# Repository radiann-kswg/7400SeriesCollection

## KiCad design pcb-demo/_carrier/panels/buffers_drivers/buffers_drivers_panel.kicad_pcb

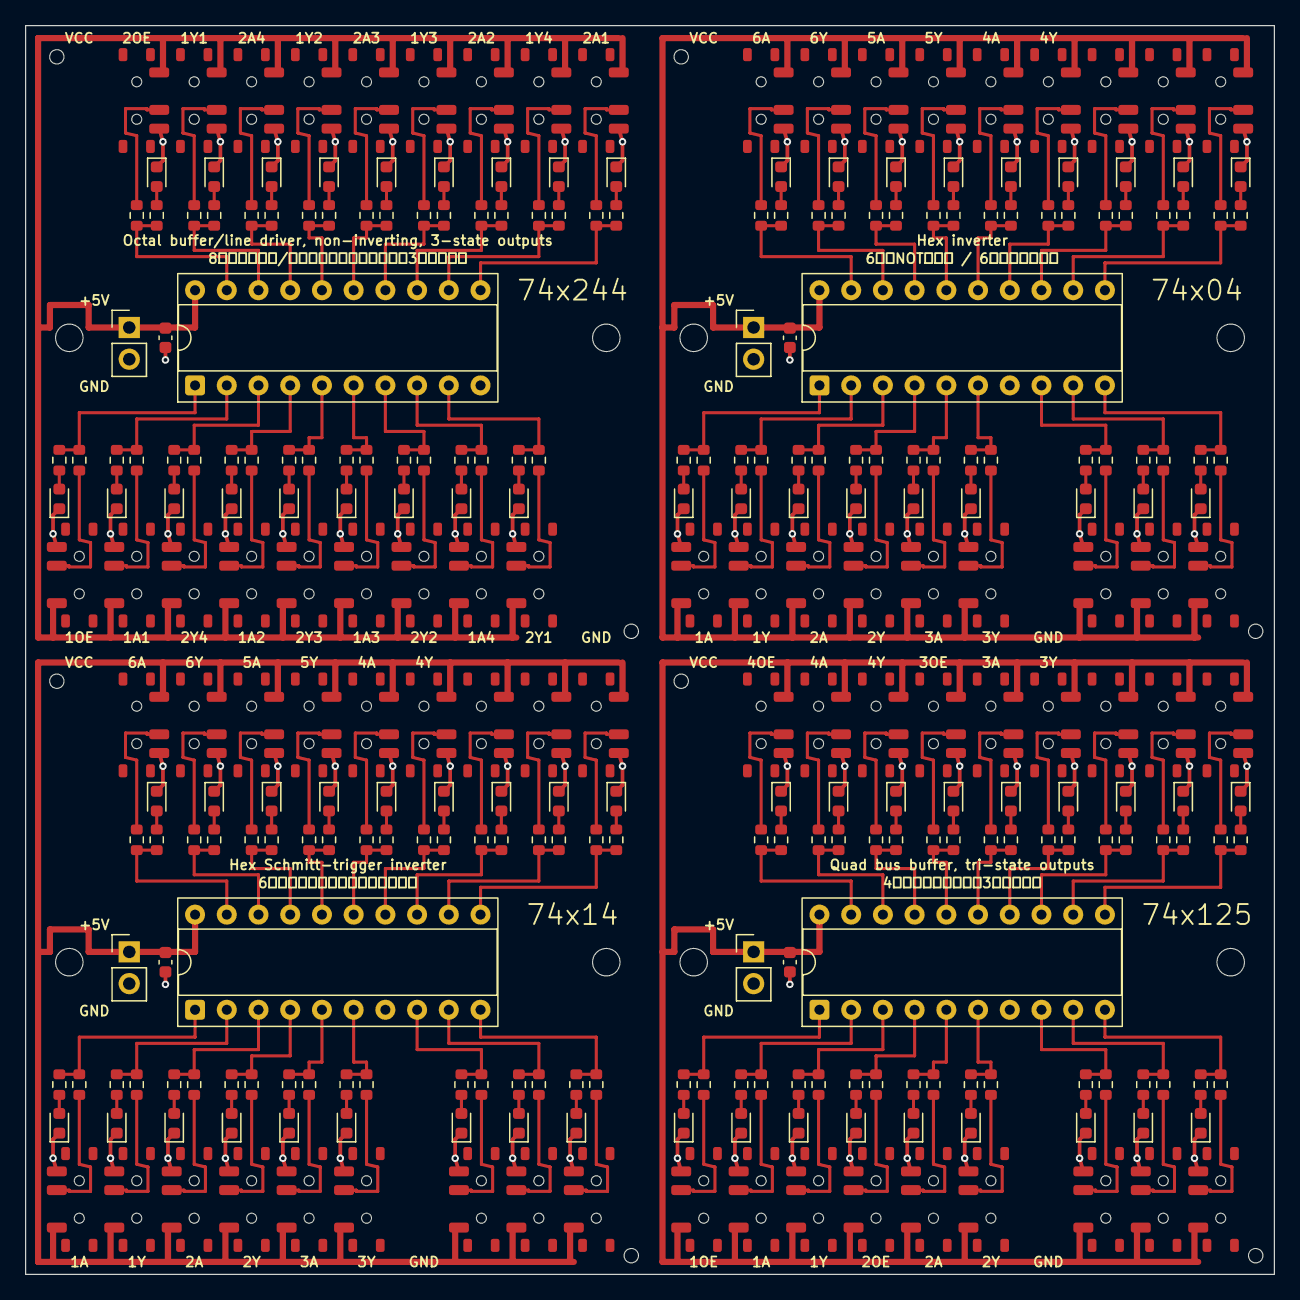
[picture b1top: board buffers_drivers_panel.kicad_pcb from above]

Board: 2 copper layers, 100.0 x 100.0 mm, 316 parts (0 on the bottom side), 224 nets.

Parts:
A_C1: 100nF; C_0603_1608Metric
A_D1, A_D2, A_D4, A_D6, A_D8, A_D11, A_D13, A_D15, A_D17, A_D19: RED; LED_0603_1608Metric
A_D3, A_D5, A_D7, A_D9, A_D12, A_D14, A_D16, A_D18: WHITE; LED_0603_1608Metric
A_J1: 5V_IN; PinHeader_1x02_P2.54mm_Vertical
A_MTG1, A_MTG2: MountingHole_2.2mm_M2
A_R1, A_R2, A_R3, A_R4, A_R5, A_R6, A_R7, A_R8, A_R9, A_R11, A_R12, A_R13, A_R14, A_R15, A_R16, A_R17, A_R18, A_R19: 4.7k; R_0603_1608Metric
A_R21, A_R22, A_R23, A_R24, A_R25, A_R26, A_R27, A_R28, A_R29, A_R31, A_R32, A_R33, A_R34, A_R35, A_R36, A_R37, A_R38, A_R39: 220; R_0603_1608Metric
A_SW1, A_SW2, A_SW3, A_SW4, A_SW5, A_SW6, A_SW7, A_SW8, A_SW9, A_SW11, A_SW12, A_SW13, A_SW14, A_SW15, A_SW16, A_SW17, A_SW18, A_SW19: MSS12C02LS-BB2.0; SW_SPDT_Shouhan_MSS12C02LS
A_TH1, A_TH2: ToolingHole_1.152mm
A_U1: DIP20_Socket_300mil; DIP-20_W7.62mm_Socket
B_C1: 100nF; C_0603_1608Metric
B_D1, B_D3, B_D5, B_D8, B_D9, B_D10, B_D11, B_D12, B_D13, B_D15, B_D17, B_D19: RED; LED_0603_1608Metric
B_D2, B_D4, B_D6, B_D14, B_D16, B_D18: WHITE; LED_0603_1608Metric
B_J1: 5V_IN; PinHeader_1x02_P2.54mm_Vertical
B_MTG1, B_MTG2: MountingHole_2.2mm_M2
B_R1, B_R2, B_R3, B_R4, B_R5, B_R6, B_R8, B_R9, B_R10, B_R11, B_R12, B_R13, B_R14, B_R15, B_R16, B_R17, B_R18, B_R19: 4.7k; R_0603_1608Metric
B_R21, B_R22, B_R23, B_R24, B_R25, B_R26, B_R28, B_R29, B_R30, B_R31, B_R32, B_R33, B_R34, B_R35, B_R36, B_R37, B_R38, B_R39: 220; R_0603_1608Metric
B_SW1, B_SW2, B_SW3, B_SW4, B_SW5, B_SW6, B_SW8, B_SW9, B_SW10, B_SW11, B_SW12, B_SW13, B_SW14, B_SW15, B_SW16, B_SW17, B_SW18, B_SW19: MSS12C02LS-BB2.0; SW_SPDT_Shouhan_MSS12C02LS
B_TH1, B_TH2: ToolingHole_1.152mm
B_U1: DIP20_Socket_300mil; DIP-20_W7.62mm_Socket
C_C1: 100nF; C_0603_1608Metric
C_D1, C_D3, C_D5, C_D8, C_D9, C_D10, C_D11, C_D12, C_D13, C_D15, C_D17, C_D19: RED; LED_0603_1608Metric
C_D2, C_D4, C_D6, C_D14, C_D16, C_D18: WHITE; LED_0603_1608Metric
C_J1: 5V_IN; PinHeader_1x02_P2.54mm_Vertical
C_MTG1, C_MTG2: MountingHole_2.2mm_M2
C_R1, C_R2, C_R3, C_R4, C_R5, C_R6, C_R8, C_R9, C_R10, C_R11, C_R12, C_R13, C_R14, C_R15, C_R16, C_R17, C_R18, C_R19: 4.7k; R_0603_1608Metric
C_R21, C_R22, C_R23, C_R24, C_R25, C_R26, C_R28, C_R29, C_R30, C_R31, C_R32, C_R33, C_R34, C_R35, C_R36, C_R37, C_R38, C_R39: 220; R_0603_1608Metric
C_SW1, C_SW2, C_SW3, C_SW4, C_SW5, C_SW6, C_SW8, C_SW9, C_SW10, C_SW11, C_SW12, C_SW13, C_SW14, C_SW15, C_SW16, C_SW17, C_SW18, C_SW19: MSS12C02LS-BB2.0; SW_SPDT_Shouhan_MSS12C02LS
C_TH1, C_TH2: ToolingHole_1.152mm
C_U1: DIP20_Socket_300mil; DIP-20_W7.62mm_Socket
D_C1: 100nF; C_0603_1608Metric
D_D1, D_D2, D_D4, D_D5, D_D8, D_D9, D_D10, D_D11, D_D12, D_D13, D_D15, D_D16, D_D18, D_D19: RED; LED_0603_1608Metric
D_D3, D_D6, D_D14, D_D17: WHITE; LED_0603_1608Metric
D_J1: 5V_IN; PinHeader_1x02_P2.54mm_Vertical
D_MTG1, D_MTG2: MountingHole_2.2mm_M2
D_R1, D_R2, D_R3, D_R4, D_R5, D_R6, D_R8, D_R9, D_R10, D_R11, D_R12, D_R13, D_R14, D_R15, D_R16, D_R17, D_R18, D_R19: 4.7k; R_0603_1608Metric
D_R21, D_R22, D_R23, D_R24, D_R25, D_R26, D_R28, D_R29, D_R30, D_R31, D_R32, D_R33, D_R34, D_R35, D_R36, D_R37, D_R38, D_R39: 220; R_0603_1608Metric
D_SW1, D_SW2, D_SW3, D_SW4, D_SW5, D_SW6, D_SW8, D_SW9, D_SW10, D_SW11, D_SW12, D_SW13, D_SW14, D_SW15, D_SW16, D_SW17, D_SW18, D_SW19: MSS12C02LS-BB2.0; SW_SPDT_Shouhan_MSS12C02LS
D_TH1, D_TH2: ToolingHole_1.152mm
D_U1: DIP20_Socket_300mil; DIP-20_W7.62mm_Socket

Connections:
A_+5V: A_C1.1, A_J1.1, A_SW1.1, A_SW2.1, A_SW3.1, A_SW4.1, A_SW5.1, A_SW6.1, A_SW7.1, A_SW8.1, A_SW9.1, A_SW11.1, A_SW12.1, A_SW13.1, A_SW14.1, A_SW15.1, A_SW16.1, A_SW17.1, A_SW18.1, A_SW19.1, A_U1.20
A_/LA1: A_D1.2, A_R1.1
A_/LA2: A_D2.2, A_R2.1
A_/LA3: A_D3.2, A_R3.1
A_/LA4: A_D4.2, A_R4.1
A_/LA5: A_D5.2, A_R5.1
A_/LA6: A_D6.2, A_R6.1
A_/LA7: A_D7.2, A_R7.1
A_/LA8: A_D8.2, A_R8.1
A_/LA9: A_D9.2, A_R9.1
A_/LA11: A_D11.2, A_R11.1
A_/LA12: A_D12.2, A_R12.1
A_/LA13: A_D13.2, A_R13.1
A_/LA14: A_D14.2, A_R14.1
A_/LA15: A_D15.2, A_R15.1
A_/LA16: A_D16.2, A_R16.1
A_/LA17: A_D17.2, A_R17.1
A_/LA18: A_D18.2, A_R18.1
A_/LA19: A_D19.2, A_R19.1
A_/P1: A_R1.2, A_R21.2, A_U1.1
A_/P2: A_R2.2, A_R22.2, A_U1.2
A_/P3: A_R3.2, A_R23.2, A_U1.3
A_/P4: A_R4.2, A_R24.2, A_U1.4
A_/P5: A_R5.2, A_R25.2, A_U1.5
A_/P6: A_R6.2, A_R26.2, A_U1.6
A_/P7: A_R7.2, A_R27.2, A_U1.7
A_/P8: A_R8.2, A_R28.2, A_U1.8
A_/P9: A_R9.2, A_R29.2, A_U1.9
A_/P11: A_R11.2, A_R31.2, A_U1.11
A_/P12: A_R12.2, A_R32.2, A_U1.12
A_/P13: A_R13.2, A_R33.2, A_U1.13
A_/P14: A_R14.2, A_R34.2, A_U1.14
A_/P15: A_R15.2, A_R35.2, A_U1.15
A_/P16: A_R16.2, A_R36.2, A_U1.16
A_/P17: A_R17.2, A_R37.2, A_U1.17
A_/P18: A_R18.2, A_R38.2, A_U1.18
A_/P19: A_R19.2, A_R39.2, A_U1.19
A_/SWC1: A_R21.1, A_SW1.2
A_/SWC2: A_R22.1, A_SW2.2
A_/SWC3: A_R23.1, A_SW3.2
A_/SWC4: A_R24.1, A_SW4.2
A_/SWC5: A_R25.1, A_SW5.2
A_/SWC6: A_R26.1, A_SW6.2
A_/SWC7: A_R27.1, A_SW7.2
A_/SWC8: A_R28.1, A_SW8.2
A_/SWC9: A_R29.1, A_SW9.2
A_/SWC11: A_R31.1, A_SW11.2
A_/SWC12: A_R32.1, A_SW12.2
A_/SWC13: A_R33.1, A_SW13.2
A_/SWC14: A_R34.1, A_SW14.2
A_/SWC15: A_R35.1, A_SW15.2
A_/SWC16: A_R36.1, A_SW16.2
A_/SWC17: A_R37.1, A_SW17.2
A_/SWC18: A_R38.1, A_SW18.2
A_/SWC19: A_R39.1, A_SW19.2
A_GND: A_C1.2, A_D1.1, A_D2.1, A_D3.1, A_D4.1, A_D5.1, A_D6.1, A_D7.1, A_D8.1, A_D9.1, A_D11.1, A_D12.1, A_D13.1, A_D14.1, A_D15.1, A_D16.1, A_D17.1, A_D18.1, A_D19.1, A_J1.2, A_SW1.3, A_SW2.3, A_SW3.3, A_SW4.3, A_SW5.3, A_SW6.3, A_SW7.3, A_SW8.3, A_SW9.3, A_SW11.3, A_SW12.3, A_SW13.3, A_SW14.3, A_SW15.3, A_SW16.3, A_SW17.3, A_SW18.3, A_SW19.3, A_U1.10
B_+5V: B_C1.1, B_J1.1, B_SW1.1, B_SW2.1, B_SW3.1, B_SW4.1, B_SW5.1, B_SW6.1, B_SW8.1, B_SW9.1, B_SW10.1, B_SW11.1, B_SW12.1, B_SW13.1, B_SW14.1, B_SW15.1, B_SW16.1, B_SW17.1, B_SW18.1, B_SW19.1, B_U1.20
B_/LA1: B_D1.2, B_R1.1
B_/LA2: B_D2.2, B_R2.1
B_/LA3: B_D3.2, B_R3.1
B_/LA4: B_D4.2, B_R4.1
B_/LA5: B_D5.2, B_R5.1
B_/LA6: B_D6.2, B_R6.1
B_/LA8: B_D8.2, B_R8.1
B_/LA9: B_D9.2, B_R9.1
B_/LA10: B_D10.2, B_R10.1
B_/LA11: B_D11.2, B_R11.1
B_/LA12: B_D12.2, B_R12.1
B_/LA13: B_D13.2, B_R13.1
B_/LA14: B_D14.2, B_R14.1
B_/LA15: B_D15.2, B_R15.1
B_/LA16: B_D16.2, B_R16.1
B_/LA17: B_D17.2, B_R17.1
B_/LA18: B_D18.2, B_R18.1
B_/LA19: B_D19.2, B_R19.1
B_/P1: B_R1.2, B_R21.2, B_U1.1
B_/P2: B_R2.2, B_R22.2, B_U1.2
B_/P3: B_R3.2, B_R23.2, B_U1.3
B_/P4: B_R4.2, B_R24.2, B_U1.4
B_/P5: B_R5.2, B_R25.2, B_U1.5
B_/P6: B_R6.2, B_R26.2, B_U1.6
B_/P8: B_R8.2, B_R28.2, B_U1.8
B_/P9: B_R9.2, B_R29.2, B_U1.9
B_/P10: B_R10.2, B_R30.2, B_U1.10
B_/P11: B_R11.2, B_R31.2, B_U1.11
B_/P12: B_R12.2, B_R32.2, B_U1.12
B_/P13: B_R13.2, B_R33.2, B_U1.13
B_/P14: B_R14.2, B_R34.2, B_U1.14
B_/P15: B_R15.2, B_R35.2, B_U1.15
B_/P16: B_R16.2, B_R36.2, B_U1.16
B_/P17: B_R17.2, B_R37.2, B_U1.17
B_/P18: B_R18.2, B_R38.2, B_U1.18
B_/P19: B_R19.2, B_R39.2, B_U1.19
B_/SWC1: B_R21.1, B_SW1.2
B_/SWC2: B_R22.1, B_SW2.2
B_/SWC3: B_R23.1, B_SW3.2
B_/SWC4: B_R24.1, B_SW4.2
B_/SWC5: B_R25.1, B_SW5.2
B_/SWC6: B_R26.1, B_SW6.2
B_/SWC8: B_R28.1, B_SW8.2
B_/SWC9: B_R29.1, B_SW9.2
B_/SWC10: B_R30.1, B_SW10.2
B_/SWC11: B_R31.1, B_SW11.2
B_/SWC12: B_R32.1, B_SW12.2
B_/SWC13: B_R33.1, B_SW13.2
B_/SWC14: B_R34.1, B_SW14.2
B_/SWC15: B_R35.1, B_SW15.2
B_/SWC16: B_R36.1, B_SW16.2
B_/SWC17: B_R37.1, B_SW17.2
B_/SWC18: B_R38.1, B_SW18.2
B_/SWC19: B_R39.1, B_SW19.2
B_GND: B_C1.2, B_D1.1, B_D2.1, B_D3.1, B_D4.1, B_D5.1, B_D6.1, B_D8.1, B_D9.1, B_D10.1, B_D11.1, B_D12.1, B_D13.1, B_D14.1, B_D15.1, B_D16.1, B_D17.1, B_D18.1, B_D19.1, B_J1.2, B_SW1.3, B_SW2.3, B_SW3.3, B_SW4.3, B_SW5.3, B_SW6.3, B_SW8.3, B_SW9.3, B_SW10.3, B_SW11.3, B_SW12.3, B_SW13.3, B_SW14.3, B_SW15.3, B_SW16.3, B_SW17.3, B_SW18.3, B_SW19.3, B_U1.7
C_+5V: C_C1.1, C_J1.1, C_SW1.1, C_SW2.1, C_SW3.1, C_SW4.1, C_SW5.1, C_SW6.1, C_SW8.1, C_SW9.1, C_SW10.1, C_SW11.1, C_SW12.1, C_SW13.1, C_SW14.1, C_SW15.1, C_SW16.1, C_SW17.1, C_SW18.1, C_SW19.1, C_U1.20
C_/LA1: C_D1.2, C_R1.1
C_/LA2: C_D2.2, C_R2.1
C_/LA3: C_D3.2, C_R3.1
C_/LA4: C_D4.2, C_R4.1
C_/LA5: C_D5.2, C_R5.1
C_/LA6: C_D6.2, C_R6.1
C_/LA8: C_D8.2, C_R8.1
C_/LA9: C_D9.2, C_R9.1
C_/LA10: C_D10.2, C_R10.1
C_/LA11: C_D11.2, C_R11.1
C_/LA12: C_D12.2, C_R12.1
C_/LA13: C_D13.2, C_R13.1
C_/LA14: C_D14.2, C_R14.1
C_/LA15: C_D15.2, C_R15.1
C_/LA16: C_D16.2, C_R16.1
C_/LA17: C_D17.2, C_R17.1
C_/LA18: C_D18.2, C_R18.1
C_/LA19: C_D19.2, C_R19.1
C_/P1: C_R1.2, C_R21.2, C_U1.1
C_/P2: C_R2.2, C_R22.2, C_U1.2
C_/P3: C_R3.2, C_R23.2, C_U1.3
C_/P4: C_R4.2, C_R24.2, C_U1.4
C_/P5: C_R5.2, C_R25.2, C_U1.5
C_/P6: C_R6.2, C_R26.2, C_U1.6
C_/P8: C_R8.2, C_R28.2, C_U1.8
C_/P9: C_R9.2, C_R29.2, C_U1.9
C_/P10: C_R10.2, C_R30.2, C_U1.10
C_/P11: C_R11.2, C_R31.2, C_U1.11
C_/P12: C_R12.2, C_R32.2, C_U1.12
C_/P13: C_R13.2, C_R33.2, C_U1.13
C_/P14: C_R14.2, C_R34.2, C_U1.14
C_/P15: C_R15.2, C_R35.2, C_U1.15
C_/P16: C_R16.2, C_R36.2, C_U1.16
C_/P17: C_R17.2, C_R37.2, C_U1.17
C_/P18: C_R18.2, C_R38.2, C_U1.18
C_/P19: C_R19.2, C_R39.2, C_U1.19
C_/SWC1: C_R21.1, C_SW1.2
C_/SWC2: C_R22.1, C_SW2.2
C_/SWC3: C_R23.1, C_SW3.2
C_/SWC4: C_R24.1, C_SW4.2
C_/SWC5: C_R25.1, C_SW5.2
C_/SWC6: C_R26.1, C_SW6.2
C_/SWC8: C_R28.1, C_SW8.2
C_/SWC9: C_R29.1, C_SW9.2
C_/SWC10: C_R30.1, C_SW10.2
C_/SWC11: C_R31.1, C_SW11.2
C_/SWC12: C_R32.1, C_SW12.2
C_/SWC13: C_R33.1, C_SW13.2
C_/SWC14: C_R34.1, C_SW14.2
C_/SWC15: C_R35.1, C_SW15.2
C_/SWC16: C_R36.1, C_SW16.2
C_/SWC17: C_R37.1, C_SW17.2
C_/SWC18: C_R38.1, C_SW18.2
C_/SWC19: C_R39.1, C_SW19.2
C_GND: C_C1.2, C_D1.1, C_D2.1, C_D3.1, C_D4.1, C_D5.1, C_D6.1, C_D8.1, C_D9.1, C_D10.1, C_D11.1, C_D12.1, C_D13.1, C_D14.1, C_D15.1, C_D16.1, C_D17.1, C_D18.1, C_D19.1, C_J1.2, C_SW1.3, C_SW2.3, C_SW3.3, C_SW4.3, C_SW5.3, C_SW6.3, C_SW8.3, C_SW9.3, C_SW10.3, C_SW11.3, C_SW12.3, C_SW13.3, C_SW14.3, C_SW15.3, C_SW16.3, C_SW17.3, C_SW18.3, C_SW19.3, C_U1.7
D_+5V: D_C1.1, D_J1.1, D_SW1.1, D_SW2.1, D_SW3.1, D_SW4.1, D_SW5.1, D_SW6.1, D_SW8.1, D_SW9.1, D_SW10.1, D_SW11.1, D_SW12.1, D_SW13.1, D_SW14.1, D_SW15.1, D_SW16.1, D_SW17.1, D_SW18.1, D_SW19.1, D_U1.20
D_/LA1: D_D1.2, D_R1.1
D_/LA2: D_D2.2, D_R2.1
D_/LA3: D_D3.2, D_R3.1
D_/LA4: D_D4.2, D_R4.1
D_/LA5: D_D5.2, D_R5.1
D_/LA6: D_D6.2, D_R6.1
D_/LA8: D_D8.2, D_R8.1
D_/LA9: D_D9.2, D_R9.1
D_/LA10: D_D10.2, D_R10.1
D_/LA11: D_D11.2, D_R11.1
D_/LA12: D_D12.2, D_R12.1
D_/LA13: D_D13.2, D_R13.1
D_/LA14: D_D14.2, D_R14.1
D_/LA15: D_D15.2, D_R15.1
D_/LA16: D_D16.2, D_R16.1
D_/LA17: D_D17.2, D_R17.1
D_/LA18: D_D18.2, D_R18.1
D_/LA19: D_D19.2, D_R19.1
D_/P1: D_R1.2, D_R21.2, D_U1.1
D_/P2: D_R2.2, D_R22.2, D_U1.2
D_/P3: D_R3.2, D_R23.2, D_U1.3
D_/P4: D_R4.2, D_R24.2, D_U1.4
D_/P5: D_R5.2, D_R25.2, D_U1.5
D_/P6: D_R6.2, D_R26.2, D_U1.6
D_/P8: D_R8.2, D_R28.2, D_U1.8
D_/P9: D_R9.2, D_R29.2, D_U1.9
D_/P10: D_R10.2, D_R30.2, D_U1.10
D_/P11: D_R11.2, D_R31.2, D_U1.11
D_/P12: D_R12.2, D_R32.2, D_U1.12
D_/P13: D_R13.2, D_R33.2, D_U1.13
D_/P14: D_R14.2, D_R34.2, D_U1.14
D_/P15: D_R15.2, D_R35.2, D_U1.15
D_/P16: D_R16.2, D_R36.2, D_U1.16
D_/P17: D_R17.2, D_R37.2, D_U1.17
D_/P18: D_R18.2, D_R38.2, D_U1.18
D_/P19: D_R19.2, D_R39.2, D_U1.19
D_/SWC1: D_R21.1, D_SW1.2
D_/SWC2: D_R22.1, D_SW2.2
D_/SWC3: D_R23.1, D_SW3.2
D_/SWC4: D_R24.1, D_SW4.2
D_/SWC5: D_R25.1, D_SW5.2
D_/SWC6: D_R26.1, D_SW6.2
D_/SWC8: D_R28.1, D_SW8.2
D_/SWC9: D_R29.1, D_SW9.2
D_/SWC10: D_R30.1, D_SW10.2
D_/SWC11: D_R31.1, D_SW11.2
D_/SWC12: D_R32.1, D_SW12.2
D_/SWC13: D_R33.1, D_SW13.2
D_/SWC14: D_R34.1, D_SW14.2
D_/SWC15: D_R35.1, D_SW15.2
D_/SWC16: D_R36.1, D_SW16.2
D_/SWC17: D_R37.1, D_SW17.2
D_/SWC18: D_R38.1, D_SW18.2
D_/SWC19: D_R39.1, D_SW19.2
D_GND: D_C1.2, D_D1.1, D_D2.1, D_D3.1, D_D4.1, D_D5.1, D_D6.1, D_D8.1, D_D9.1, D_D10.1, D_D11.1, D_D12.1, D_D13.1, D_D14.1, D_D15.1, D_D16.1, D_D17.1, D_D18.1, D_D19.1, D_J1.2, D_SW1.3, D_SW2.3, D_SW3.3, D_SW4.3, D_SW5.3, D_SW6.3, D_SW8.3, D_SW9.3, D_SW10.3, D_SW11.3, D_SW12.3, D_SW13.3, D_SW14.3, D_SW15.3, D_SW16.3, D_SW17.3, D_SW18.3, D_SW19.3, D_U1.7

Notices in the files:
pcb-demo/_carrier/panels/buffers_drivers/buffers_drivers_panel.kicad_pcb:
MIT License
